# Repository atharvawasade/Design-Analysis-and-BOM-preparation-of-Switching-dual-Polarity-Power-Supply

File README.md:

# Design-Analysis-and-BOM-preparation-of-Switching-dual-Polarity-Power-Supply

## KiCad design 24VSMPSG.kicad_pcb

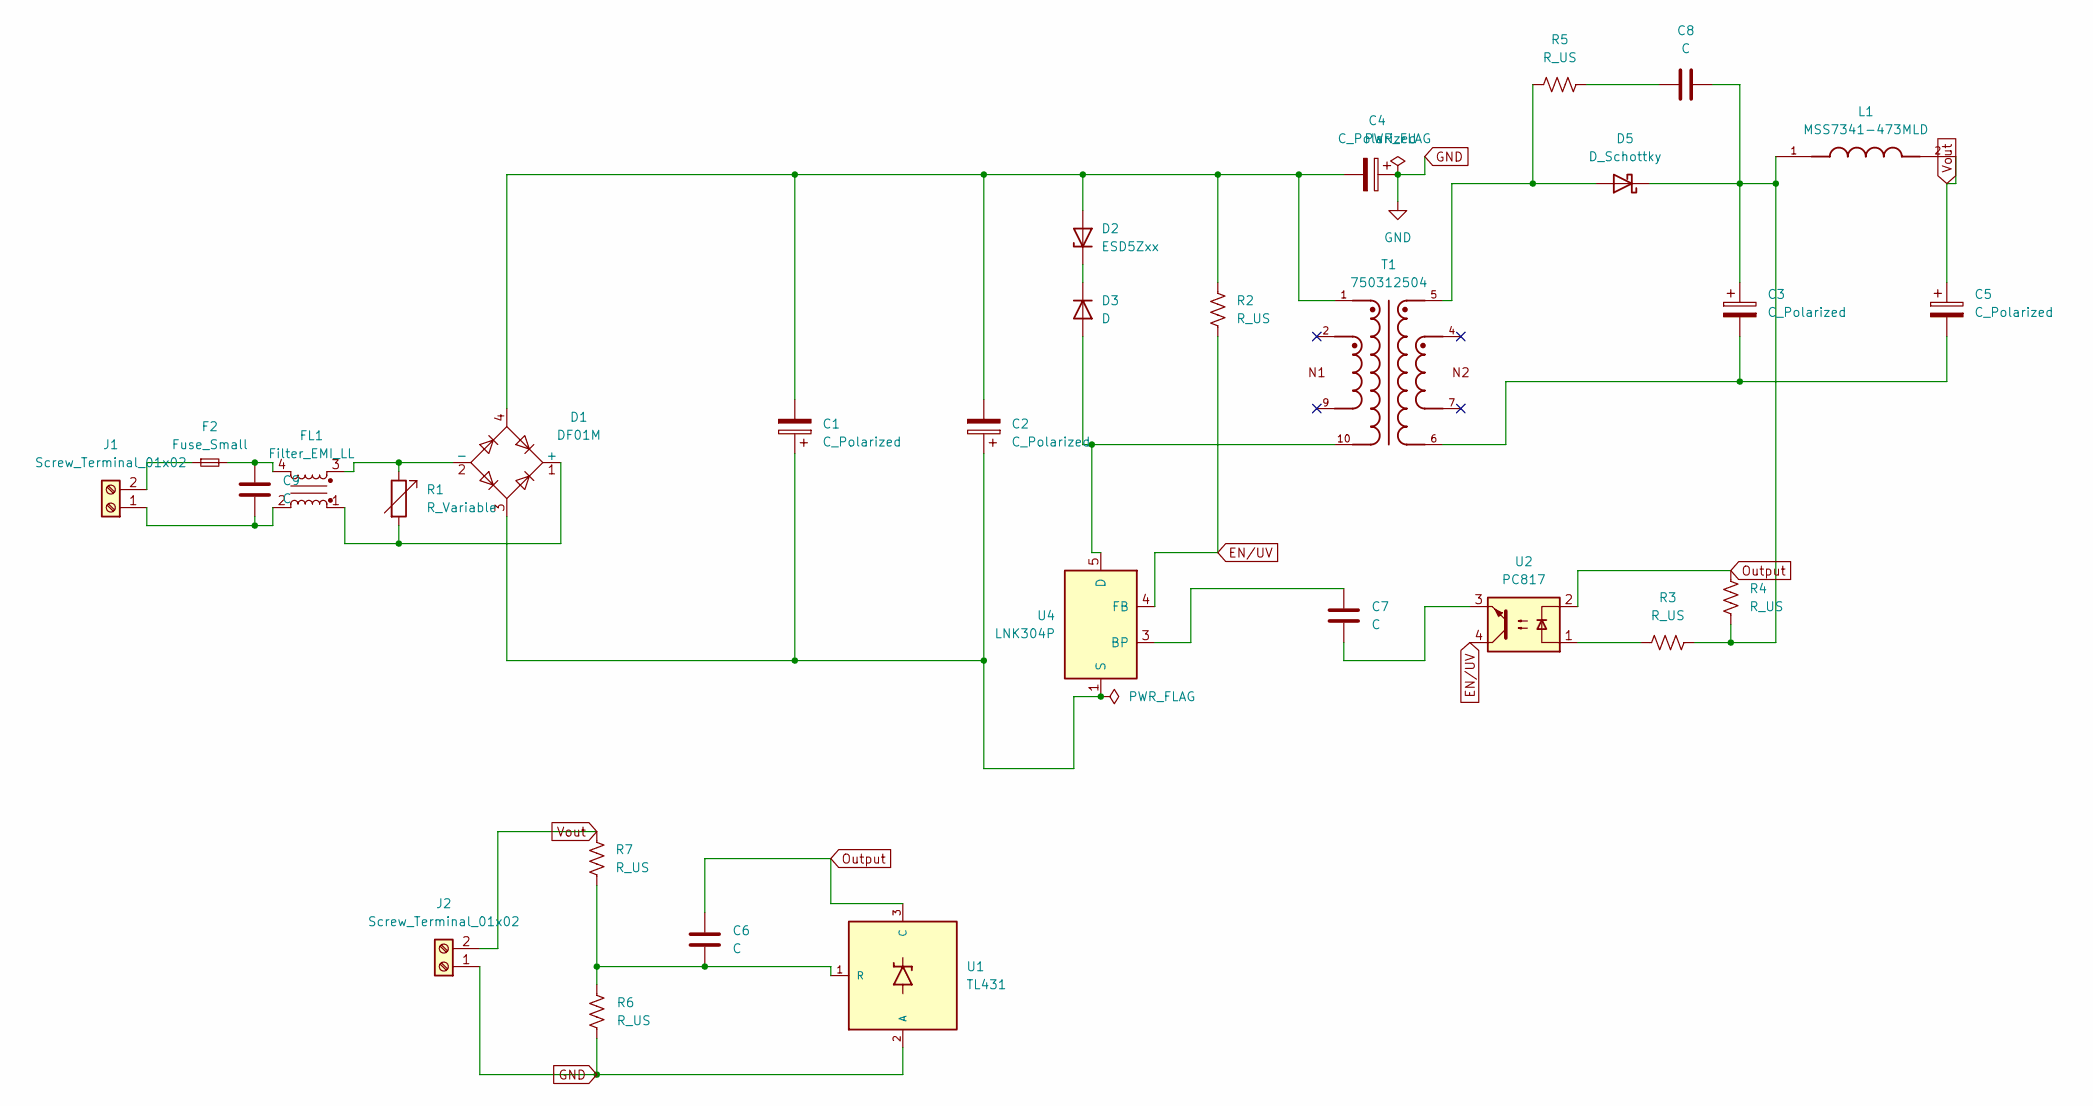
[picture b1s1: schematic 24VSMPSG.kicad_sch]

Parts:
C1, C2: C_Polarized; CP_Axial_L10.0mm_D4.5mm_P15.00mm_Horizontal
C3, C5: C_Polarized; C_Radial_D10.0mm_H20.0mm_P5.00mm
C4: C_Polarized; C320C
C6: C; CP_Radial_D4.0mm_P1.50mm
C7: C; C320C
C8: C; CP_Radial_D4.0mm_P2.00mm
C9: C; CP_Axial_L10.0mm_D4.5mm_P15.00mm_Horizontal
D1: DF01M; Diode_Bridge_DIP-4_W7.62mm_P5.08mm
D2: ESD5Zxx; D_5KPW_P7.62mm_Vertical_AnodeUp
D3: D; D_5KPW_P7.62mm_Vertical_AnodeUp
D5: D_Schottky; D_5KP_P7.62mm_Vertical_AnodeUp
F2: Fuse_Small; Fuse_BelFuse_0ZRE0012FF_L8.3mm_W3.8mm
FL1: Filter_EMI_LL; Filter_FILTERCON_1FPxx
J1, J2: Screw_Terminal_01x02; TerminalBlock_bornier-2_P5.08mm
L1: MSS7341-473MLD; L_Axial_L14.5mm_D5.8mm_P25.40mm_Horizontal_Fastron_HBCC; PARTREV 02/08/17
R1: R_Variable; R_Axial_DIN0204_L3.6mm_D1.6mm_P1.90mm_Vertical
R2, R3, R4, R5, R6, R7: R_US; R_Axial_DIN0204_L3.6mm_D1.6mm_P1.90mm_Vertical
T1: 750312504; Transformer_Wuerth_750343373; PART-NUMBER 750312504
U1: TL431; TO-92
U2: PC817; DIP-4_W7.62mm
U4: LNK304P; PowerIntegrations_PDIP-8B

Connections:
EN/UV: R2.2, U2.4, U4.4 (FB)
GND: C4.1, J2.1, R6.2, U1.2 (A)
unnamed: C1.1, C2.1, D1.3, U4.1 (S), U4.2 (S), U4.7 (S), U4.8 (S)
unnamed: C3.2, C5.2, T1.6
unnamed: C7.2, U2.3
unnamed: C8.1, R5.1
unnamed: C9.2, F2.2, FL1.4
unnamed: D1.1 (+), FL1.1, R1.2
unnamed: D1.2 (-), FL1.3, R1.1
unnamed: C1.2, C2.2, C4.2, D1.4, D2.2 (A), R2.1, T1.1
unnamed: D2.1 (K), D3.1 (K)
unnamed: D3.2 (A), T1.10, U4.5 (D)
unnamed: D5.2 (A), R5.2, T1.5
unnamed: C3.1, C8.2, D5.1 (K), L1.1, R3.1, R4.2
unnamed: C9.1, FL1.2, J1.1
unnamed: F2.1, J1.2
unnamed: R3.2, U2.1
unnamed: C6.2, R6.1, R7.2, U1.1 (R)
unnamed: C7.1, U4.3 (BP)
Output: C6.1, R4.1, U1.3 (C), U2.2; also elsewhere on the board
Vout: C5.1, J2.2, L1.2, R7.1

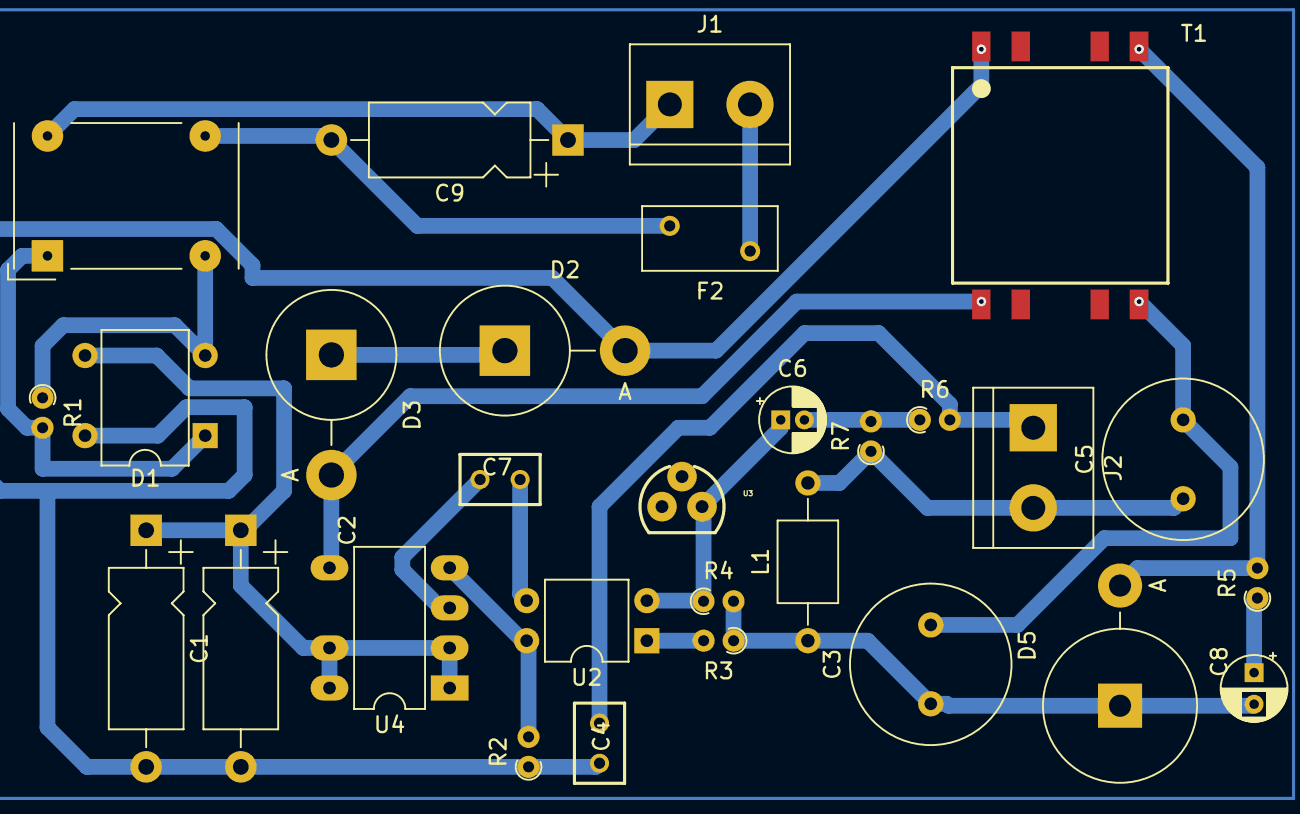
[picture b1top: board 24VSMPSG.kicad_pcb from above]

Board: 2 copper layers, 29 parts (0 on the bottom side), 21 nets.

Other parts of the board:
U3: TL431DBV; TO-92

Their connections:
Output: U3.3 (K); also elsewhere on the board
